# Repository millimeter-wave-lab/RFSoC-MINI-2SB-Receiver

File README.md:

# RFSoC MINI 2SB Receiver
This repository contains Simulink models for **(Ideal) Digital Sideband Separation** on RFSoC 4x2 for Southern Millimeter Wave Telescope (or Southern Mini). Python and C++ scripts for initialization, control, and data analysis are included.

## Simulink Models
The `64_bits_models/` and `32_bits_models/` folder contains Simulink designs for FPGA programming. Each model is built using Xilinx System Generator for DSP and targets FPGA boards such as the Zynq UltraScale+ RFSoC. To design the spectrometers, [CASPER toolflow](https://casper-toolflow.readthedocs.io/projects/tutorials/en/latest/tutorials/rfsoc/tut_getting_started.html) must be installed.

### 64 bits models (Experimental Only)
Three 64-bits models were designed and used in laboratory for test ideal sideband separation. These models have a 1.96608 GHz bandwidth and 64-bit BRAMs, and are available for the next spectral resolutions:
- 2048 channels
- 8192 channels
- 16384 channels

### 32 bits models
Due to the 32-bit limitation of the radiotelescope microcontroller (PIC32), this repository includes spectrometer models with 32-bit BRAMs. These models are available for different spectral resolutions:
- 8192 channels
- 16384 channels
- 32768 channels
- 65536 channels (implemented in two separate models due to resource limitations.)

Each model includes:
- 32-bit BRAM blocks for data acquisition, named `synth0_i` and `synth1_i` for the high-resolution spectrometer, and `re_bin_synth0_i` and `re_bin_synth1_i` for the parallel 512-channel spectrometer.
- Reset accumulation control.
- Bits re-quantization blocks.

> **Note:** For the 65536-channel models, the **User IP Clock Rate** in the **RFSoC 4x2** Simulink block **was set to 122.88 MHz**. This setting is required to match the **Required AXI4-Stream Clock Rate** of the **RFDC** block; otherwise, the model will fail to compile.  

## Python Scripts

This repository includes Python scripts for initializing the RFSoC, configuring registers, capturing data, and performing post-processing (e.g., plotting spectra, calculate SRR, etc.). 

| File | Description |
|------|-------------|
| `anim_dss_spectrum_1966mhz.py` | Plots the spectrum in real time for a 1.96608 GHz bandwidth. <br>**Usage:** `python anim_dss_spectrum_1966mhz.py <HOSTNAME_or_IP> <Nfft Size> <Data Output Width>` |
| `anim_dss_spectrum_65536ch_1966mhz.py` |Plots the spectrum in real time for 65536-channel models, selects first or second half of the spectrum via `part` argument. <br>**Usage:** `python anim_dss_spectrum_65536ch_1966mhz.py <HOSTNAME_or_IP> <Nfft Size> <Data Output Width> <part>` (where `part` = 1 or 2) |
| `sweep_srr_plot_1966mhz.py` | Performs a sweep across the full bandwidth and computes the Sideband Rejection Ratio (SRR). <br>**Usage:** `python sweep_srr_plot_1966mhz.py <HOSTNAME_or_IP> <Nfft Size> <RF Instrument IP address> <Data Output Width>` |
| `sweep_srr_plot_65536ch_1966mhz.py` | Sweeps a portion of the bandwidth and calculates the Sideband Rejection Ratio (SRR) for 65536-channel models. The script selects either the first or second half of the spectrum using the `part` argument. <br>**Usage:** `python sweep_srr_plot_65536ch_1966mhz.py <HOSTNAME_or_IP> <Nfft Size> <RF Instrument IP address> <Data Output Width> <part>` (where `part` = 1 or 2) |
| `sweep_ph_plot_1966mhz.py` | Sweeps across the full bandwidth and calculates phase difference between I and Q outputs. Only works for 64-bits models. <br>**Usage:** `python sweep_ph_plot_1966mhz.py <HOSTNAME_or_IP> <Nfft Size> <RF instrument IP address> <Data Output Width>` |
| `plot_srr_ph_diff.py` | Plots SRR or phase difference from a CSV file. <br>**Usage:** `python plot_srr_ph_diff.py` |
| `plot_srr_65536ch.py` | Plots SRR for 65536-channels spectrometer models. Reads two CSV files corresponding to first and second part of the bandwidth. <br>**Usage:** `python plot_srr_65536ch.py` |
| `test_spec_cnt.py` | Tests the accumulation counter. <br>**Usage:** `python test_spec_cnt.py` |

## Mini Implementation

This section includes Python and C++ scripts used for communication testing and deployment of the RFSoC-based spectrometer system at the Southern Millimeter Wave Telescope (Mini).

### Python Scripts

| File | Description |
|------|-------------|
| `rfsoc4x2_spec_ini.py` | Initializes and programs the RFSoC with the selected spectrometer model. <br>**Usage:** `python rfsoc4x2_spec_ini.py` |
| `cpp_interface.py` | Python interface that repeatedly requests spectra via the C++ client and measures the response time. Results are logged to a `.csv` file. <br>**Usage:** `python cpp_interface.py` |
| `plot.py` | Plots delays recorded during spectrum acquisition requests. <br>**Usage:** `python plot.py` |
| `rfsoc_mini_client.py` | Python client script used in the Mini radiotelescope Data Server. Requests spectra and transmits them to the PIC32 microcontroller. <br>**Usage:** `python rfsoc_mini_client.py` |

### C++ Scripts

| File | Description |
|------|-------------|
| `rfsoc_<n_ch>ch_<mode>_server.cpp` | C++ server that runs on the RFSoC. It waits for incoming client connections and sends spectrum data. Located in the `rfsoc_server` folder. <br><br>**Parameters:**<br>- `n_ch`: number of channels, valid values are `8192`, `16384`, or `32768`.<br>- `mode`: operation mode, either `cal` (calibrated) or `ideal` (ideal model).|
| `cpp_socket.cpp` | C++ client that connects to the RFSoC server and requests spectrum data. It is compiled as a Python extension using `pybind11`, enabling integration with Python scripts. |

### Execution Flow

Below is the standard sequence to run the RFSoC spectrometer system:

1. **Program the RFSoC with the spectrometer bitstream**  
   Load the selected spectrometer model onto the RFSoC using the initialization script:

   ```bash
   python rfsoc4x2_spec_ini.py
   ```
2. **Start the RFSoC Server**  
   Connect to the RFSoC via SSH:
   ```bash
   ssh casper@<rfsoc-ip>
   ```
   Then, compile and run the server. The following example uses the 8192-channel server for the ideal model:

   ```bash
   g++ rfsoc_8192ch_ideal_server.cpp -o rfsoc_8192ch_ideal_server

   sudo ./rfsoc_8192ch_ideal_server
   ```
   **Note:** For 65536-channel models, use the `32768`-channel server. The bitstream `dss_ideal1_65536ch_32bits_reset_1966mhz_cx.fpg` observes the **first** 32768 channels of the bandwidth, while `dss_ideal2_65536ch_32bits_reset_1966mhz_cx.fpg` observes the **second** 32768 channels. 
3. **Compile the C++ Socket Client**  
   On the control computer, compile:

   ```bash
   c++ -O3 -Wall -shared -std=c++11 -fPIC `python3 -m pybind11 --includes` cpp_socket.cpp -o cpp_socket`python3-config --extension-suffix`
   ```
4. **Run the Python Interface**  
   Choose one of the following scripts depending on the use case:

   - **Laboratory testing interface** – This script repeatedly requests spectra via the C++ client and measures the response time. It logs the delays in a `.csv` file for later analysis.

     ```bash
     python cpp_interface.py
     ```

   - **Mini telescope deployment interface** – This script runs on the Data Server located at the Mini telescope site. It requests spectra from the RFSoC and sends them directly to the PIC32 microcontroller, without logging timing information.

     ```bash
     python rfsoc_mini_client.py
     ```

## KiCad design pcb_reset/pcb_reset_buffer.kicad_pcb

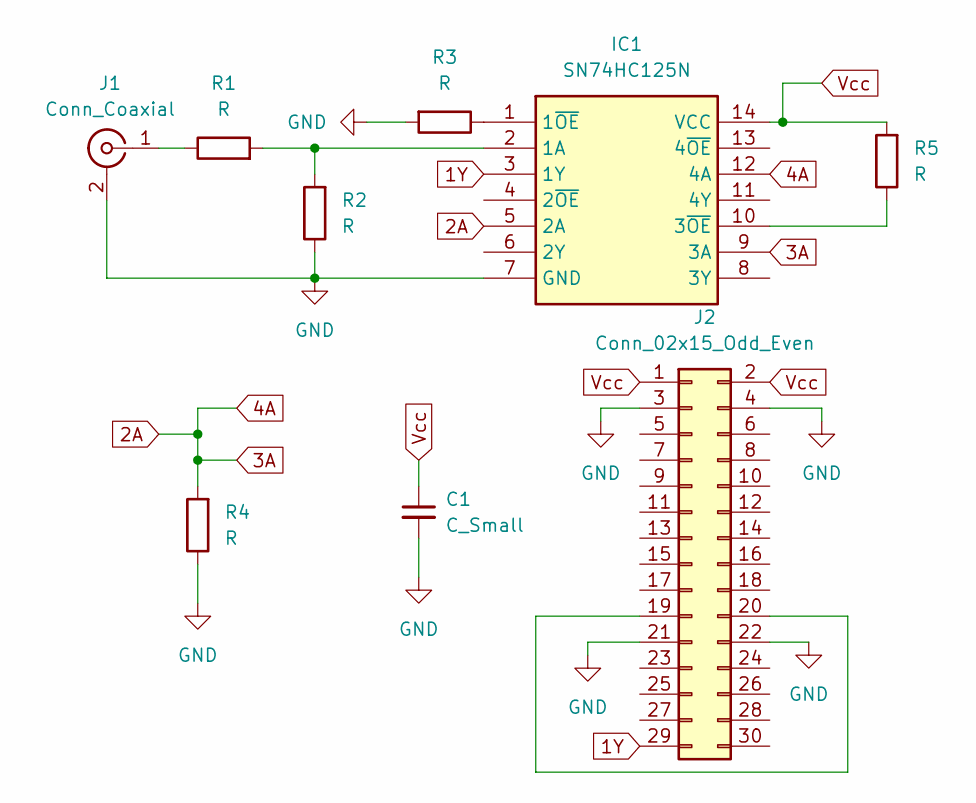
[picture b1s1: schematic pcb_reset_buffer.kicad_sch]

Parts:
C1: C_Small; C_Disc_D3.0mm_W2.0mm_P2.50mm
IC1: SN74HC125N; DIP794W53P254L1930H508Q14N; Manufacturer_Part_Number SN74HC125N
J1: Conn_Coaxial; SMA_Samtec_SMA-J-P-H-ST-EM1_EdgeMount
J2: Conn_02x15_Odd_Even; PinHeader_2x15_P2.54mm_Vertical
R1, R2, R3, R4, R5: R; R_Axial_DIN0207_L6.3mm_D2.5mm_P10.16mm_Horizontal

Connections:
1Y: IC1.3 (1Y), J2.29
2A: IC1.5 (2A), IC1.9 (3A), IC1.12 (4A), R4.2
GND: C1.2, IC1.7 (GND), J1.2 (Ext), J2.3, J2.4, J2.21, J2.22, R2.1, R3.2, R4.1
unnamed: IC1.2 (1A), R1.2, R2.2
unnamed: IC1.1 (1~OE), R3.1
unnamed: IC1.10 (3~OE), R5.1
unnamed: J1.1 (In), R1.1
unnamed: J2.19, J2.20
Vcc: C1.1, IC1.14 (VCC), J2.1, J2.2, R5.2

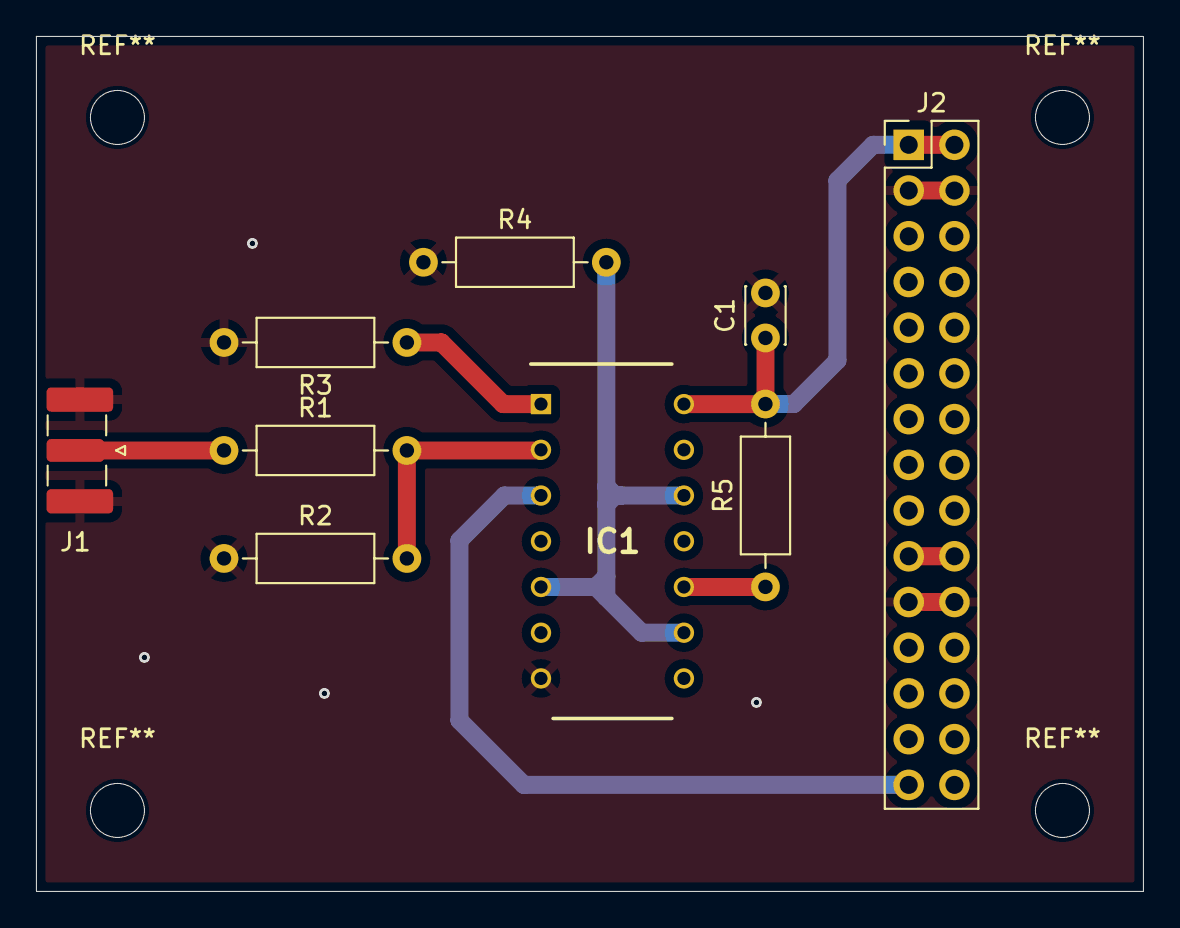
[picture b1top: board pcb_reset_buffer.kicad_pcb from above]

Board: 2 copper layers, 61.5 x 47.5 mm, 9 parts (0 on the bottom side), 9 nets.

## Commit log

2024-09-26 script for plotting SRR on 1966mhz bandwidth
2024-09-26 plot measured phase difference between IF outputs
2024-09-26 fpg_prebuilt path changed
2024-09-26 script to visualize spectrum on both IF outputs and SRR
2024-09-26 scridigital sideband separation RFSoC model
2024-09-26 digital sideband separation RFSoC model
2024-09-27 optparse library replaced by argpase
2024-09-27 show real time phase difference between IF Outputs
2024-10-09 FFT size increased to 8192, hostname path modified, and instrument.write() changed
2024-10-09 FFT size increased to 8192, and hostname path modified
2024-10-09 Digital Sideband Separation models
2024-10-09 Models replaced by new
2024-10-17 add fft size as input
2025-01-02 Updated Digital Sideband Separation models
2025-01-02 Script to test Reset signal with a spectrum counter
2025-01-02 Add number of bits of BRAMs as input, and scripts more documented
2025-01-02 2048ch, 8192ch and 16384ch directories deleted
2025-01-08 return values inverted in get_vacc_data_power() function
2025-01-08 parser.add_argument() error fixed
2025-06-12 Updated models for different resolutions
2025-06-12 CSV files with SRR and phase difference measurements. Use 'plot_srr_ph_diff.py' script to plot.
2025-06-12 Python script to read CSV files, and plot SRR and phase difference.
2025-06-12 Save measurements to a CSV file.
2025-06-12 Added 512-size FFT reading. Save measurements to a CSV file.
2025-06-12 Added 512-size FFT reading.
2025-06-12 Script documentation updated.
2025-06-12 Spectrum visualization for the 65536-size FFT spectrometer.
2025-06-12 C++ script for TCP/IP server. Must be executed from RFSoC terminal
2025-06-12 Initialization script for RFSoC 4x2.
2025-06-12 C++ script for create socket and connect with RFSoC server.
2025-06-12 Python script used as interface for test delays on data acquisition.
2025-06-12 Visualization of time delays on data acquisition.
2025-06-16 Mini data server client and RFSoC initialization
2025-06-16 Change name file and delete repeated file
2025-06-19 First channel read eliminated for the second model
2025-06-19 Performs a sweep and computes the SRR for both high resolution spectrometers
2025-07-08 PCB gerber files designed on KiCad for Reset control
2025-07-08 Script for calibration data reading and calibrates sideband separating spectrometer
2025-07-09 Models for calibrated spectrometers.
2025-07-09 .Xil folder removed
2025-07-09 Ideal sideband separation models renamed
2025-07-09 Calibrated sideband separation models renamed
2025-07-10 Update argument descriptions in script header
2025-07-15 Update to receive 'spectrum part' as argument. Update documentation.
2025-07-15 Measurements for high resolution spectrometer.
2025-07-15 SRR plot for high resolution spectrometer.
2025-07-28 RFSoC server for each resolution model
2025-07-29 Ensure request waits until all spectrum bytes are received
2025-07-31 Client now loads appropiate accumulation length according to RFSoC model
2025-07-31 RFSoC server moved to 'rfsoc_server' folder. Now available for each resolution model.
2025-07-31 Client now loads appropiate accumulation length according to RFSoC model. Channels to read is a parameter of the function 'process_RFSoC_request()' now.
